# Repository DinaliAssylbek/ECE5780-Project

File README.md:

Team Members:
Hayden Walpole; Undergraduate; Computer Engineering 
Andy Tran; Undergraduate; Computer Engineering 
Dinali Assylbek; Undergraduate; Computer Engineering
Stein Witt; Undergraduate; Mechanical Engineering

-File Directory-
CAD_FILES: file for the Platic Housing of our Watch Monitor
Datasheetes: BOM and datasheets for the given componants
HealthMonitor: Main Code file to be used to Flash the board with initialization and reading the sensor
Nucleo_Board_Testing: Code used to Test Dev board and Flashing with our 6-pin SWD cable.
PCB: PCB Scematic files and Board Design
Photos: Pictures of the development and debugging process. Also contains helpful refrence photos
Analog Discovery Code Attempts: Code we tried to use to communicate over I2C using Waveform with an analog discovery.

Milestone 4 Powerpoint presentation: https://1drv.ms/p/c/c447666567076377/EbAtq3pLUSZKpYCg5cf9b-IBzeUnjeowH9_FPiCp1k7Zxw?e=1KSI1v

You need to install the following for the STM32 VSCode extension to work.

-STMCubeIDE
-STMCubeMX
-STMCLT
-STMMCU
ECE 5780 – ReadMe Documentation
Project Name: Wearable Health Monitor 
Purpose:
The purpose of this project is to design, assemble, and program a custom PCB for a compact wearable device that allows a person to continuously monitor their heart rate and blood oxygen levels (SpO₂). The device provides real-time feedback when readings fall outside safe thresholds by using an onboard vibrating motor and status LEDs. It is intended to be a low-power, discreet health monitoring solution suitable for everyday use.
Functionality:
The Wearable Health Monitor includes the following features:
•	Real-Time Heart Rate Monitoring: Uses the MAX30102 optical sensor to continuously measure the user’s heart rate.
•	SpO₂ (Blood Oxygen) Monitoring: Calculates and updates the user’s oxygen saturation level every few seconds.
•	Vibration Motor and Status LED: Activates when heart rate or oxygen levels are outside the defined safe range.
•	Power Supply: Currently powered via USB-C. However, the board can run on a battery if connected through the USB-C port (e.g., with a USB-C battery pack).

•	Optional Bluetooth: The board supports Bluetooth; however, Bluetooth functionality is not implemented in the driver code.

Setup Instructions:
1.	PCB Fabrication:
To manufacture the board, use the schematic and PCB layout files found in the PCB directory of the GitHub repository. These files are compatible with common PCB manufacturers such as PCBWay (used for this project). Before submission, make sure to generate and include:
o	Gerber files
o	Bill of Materials (BOM)
o	Pick-and-place files (if needed)
The schematic for this project is presented below: 
 
2.	Assembly Guidelines:
Component assembly is a critical step due to the small form factor and use of QFN or similar packages that do not expose all pins. Many components have pads located underneath, making traditional soldering difficult.
Important:
Avoid using a reflow oven. While convenient, reflow can result in unreliable connections or floating components. Instead:
o	Use solder paste with a precision heat gun
o	Inspect each connection carefully under magnification
However, if your manufacturer offers services for PCB assembly, it is advisable to have them assemble the board for you. This is to avoid any potential problems regarding the PCB itself.
Note: Be careful when handling the board after assembly, the parts are delicate!
3.	Programming the Board:
The board is programmed using a dedicated ST-Link programmer with a 6-pin Tag-Connect cable.
o	To enter bootloader mode:
	Power the board
	Press and hold the BOOT button
	Momentarily ground the NRST (reset) pin (accessible via the ST-Link header)
	Release NRST while continuing to hold BOOT for a few seconds
Note: While USB-C bootloader programming is theoretically possible, it has not been tested. The ST-Link method is the recommended and verified approach.
When using the ST-Link, bootloader mode is not required.
4.	Firmware Setup:
o	Clone the repository and open the Health Monitor project
o	All source files are in the Core directory
o	A custom library for the MAX30102 sensor is included
Pin Configuration:
o	PB8 → I2C1_SCL (Clock Line)
o	PB9 → I2C1_SDA (Data Line)
o	Pin 12 → Controls both the vibration motor and status LED
The project builds and runs best using the STM32CubeIDE and STM32CubeProgrammer.
Once the board is powered and connected via ST-Link:
o	Build the project
o	Flash the firmware using the programmer
o	The device will begin operation immediately after flashing

5.	Troubleshooting
In the case where you may encounter issues with the PCB, there are several steps you can take to diagnose and resolve problems:
o	No Power to the Board:
o	Confirm that the USB-C cable is securely connected and providing power. If not, try to use a different cable to supply power to the chip
o	Check the voltages along all the voltage lines (3.3V and 1.8V) using a multimeter.
o	Ensure all power-related components (LDO regulator, bypass caps, etc.) are properly soldered. If the board starts to heat up rapidly, use a thermal camera to help check for shorts.
o	Sensor Not Detected (MAX30102):
o	Double-check I2C connections (PB8 for SCL, PB9 for SDA).
o	Use a logic analyzer or oscilloscope to verify I2C traffic.
o	Confirm the sensor that the registers and addresses are configured correctly.
o	Programming Issues:
o	Make sure the ST-Link is correctly connected via the Tag-Connect header.
o	Ensure that the Tag-Connect and ST-Link work. This can be achieved by uploading code to a breakout board.
o	Ensure that all user code lies in the correct regions as defined in the cube IDE. Check that all the correct header files are included and desired code is not commented out.
o	Miscellaneous Issues:
o	If the PCB fails to work, inspect solder joints again for bridges or incomplete connections. Examine under a microscope. If possible, reach out to someone with a more trained eye to look at the soldering job.
o	Make sure components on the board are assembled correctly. This means making sure the orientations of the components are in the right place, and no components are missing.
o	Be careful when disconnecting the cable when flashing the board. This potentially could cause you to brick the chip on the PCB. 

Videos Used as Refrences:
Schematic Design Video: https://www.youtube.com/watch?v=nkHFoxe0mrU
PBC Design Video: https://www.youtube.com/watch?v=PlXd3lLZ4vc&t=10184s

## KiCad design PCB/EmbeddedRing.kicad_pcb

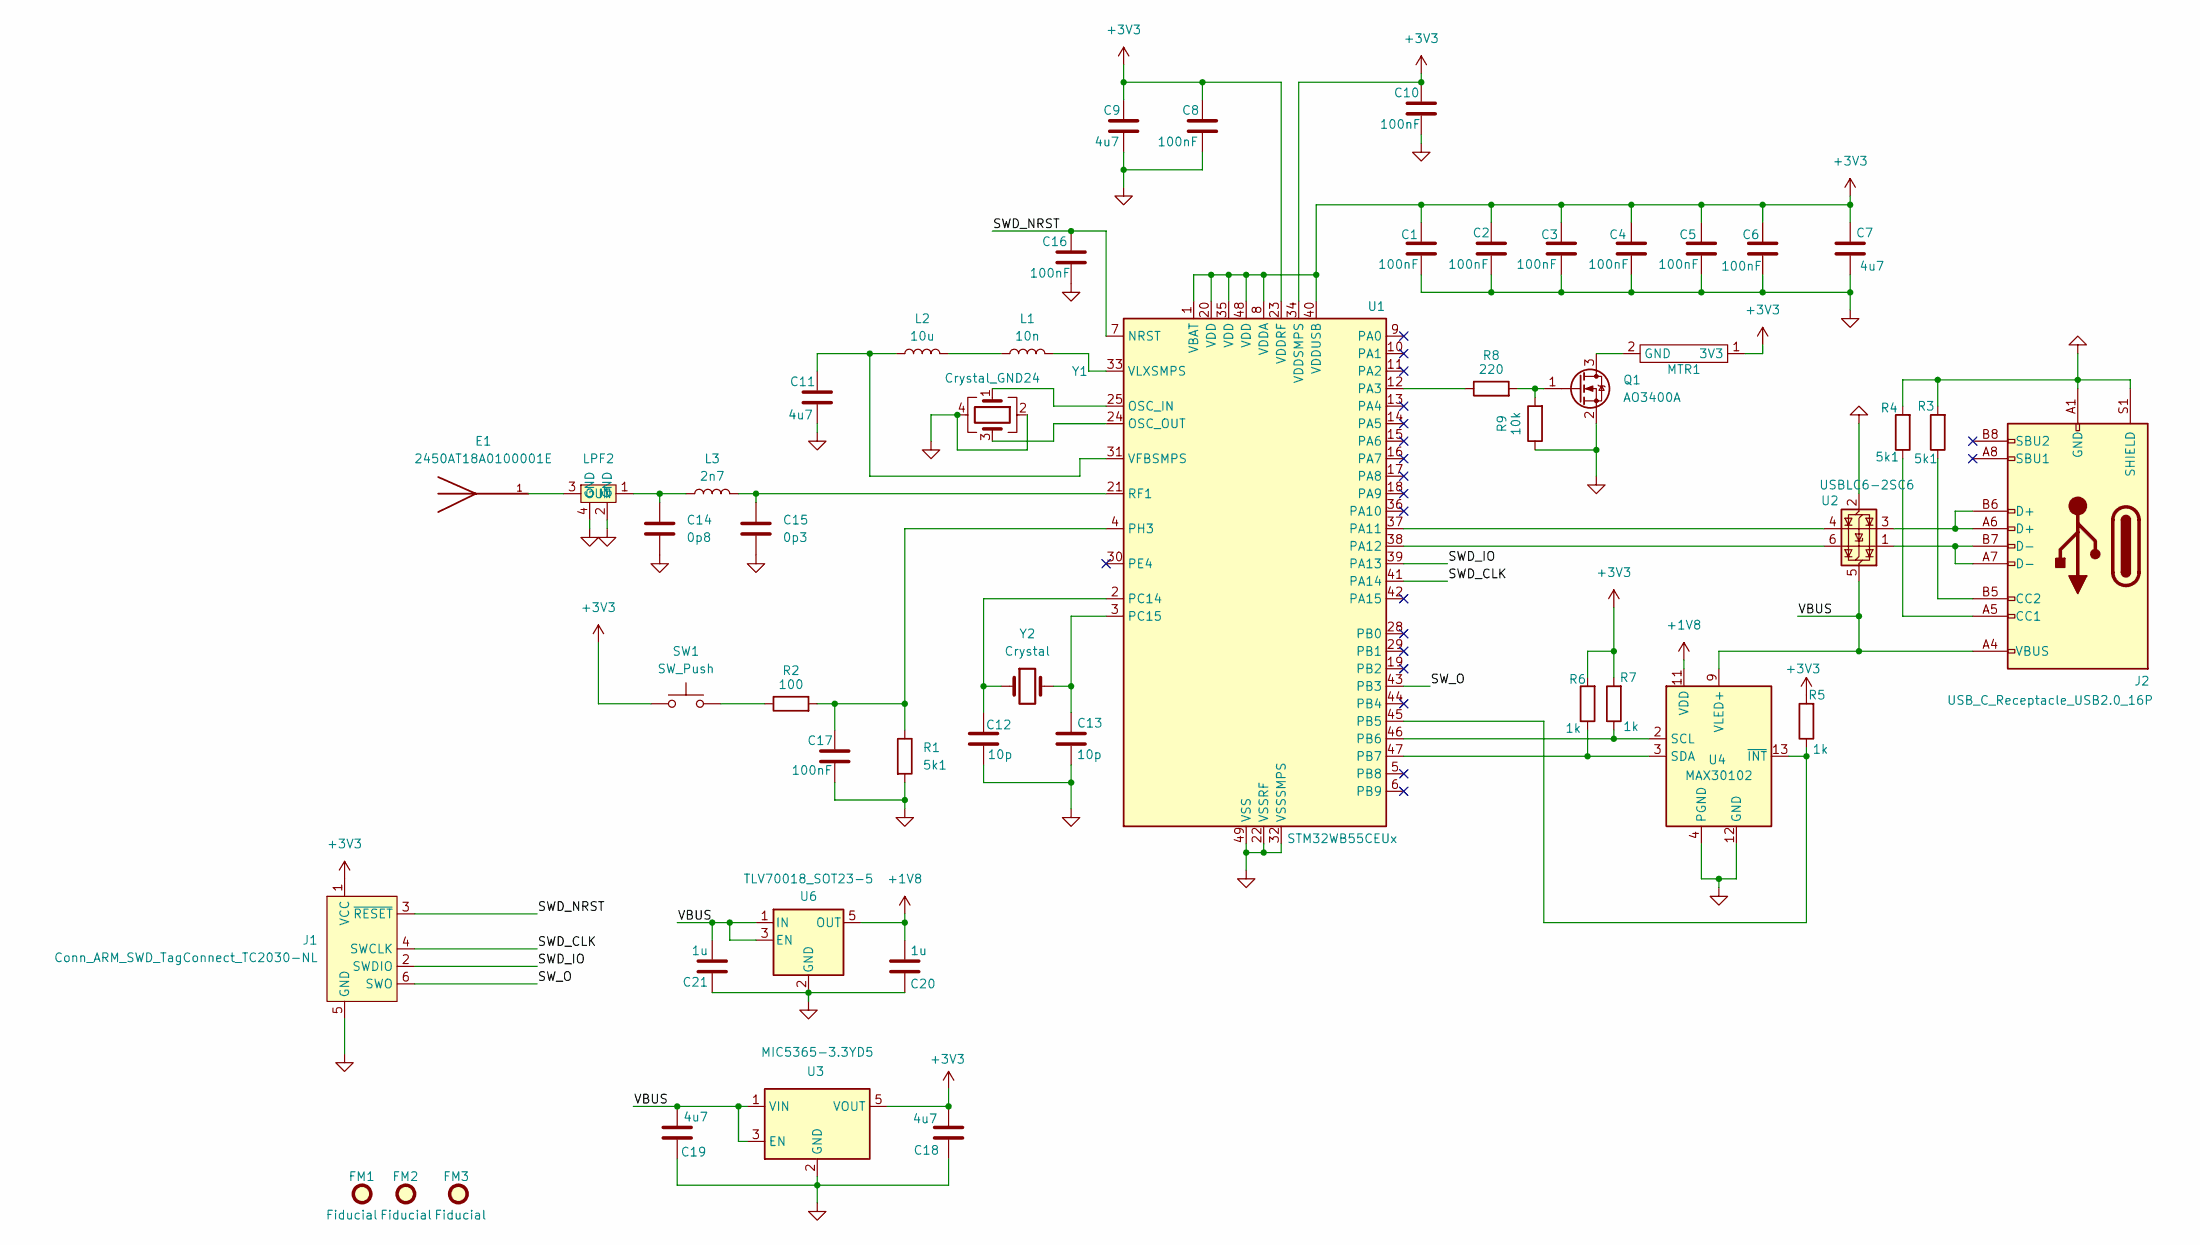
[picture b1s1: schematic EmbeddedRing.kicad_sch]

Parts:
C1, C2, C3, C4, C5, C6, C8, C10, C16, C17: 100nF; C_0402_1005Metric; Manufacturer Part Number 04026C104KAT2A
C7: 4u7; C_0603_1608Metric; Manufacturer Part Number 0603YD475MAT2A
C9, C11: 4u7; C_0402_1005Metric_Pad0.74x0.62mm_HandSolder; Manufacturer Part Number 0603YD475MAT2A
C12, C13: 10p; C_01005_0402Metric; Manufacturer Part Number KGM05ACG1H100JN
C14: 0p8; C_01005_0402Metric; Manufacturer Part Number GRM1555C1HR80BA01D
C15: 0p3; C_01005_0402Metric; Manufacturer Part Number GRM1555C1HR30WA01D
C18, C19: 4u7; C_0201_0603Metric_Pad0.64x0.40mm_HandSolder; Manufacturer Part Number 0603YD475MAT2A
C20, C21: 1u; C_0201_0603Metric_Pad0.64x0.40mm_HandSolder; Manufacturer Part Number 0603B105K100XD
E1: 2450AT18A0100001E; antennaa; PARTREV 4.0
FM1, FM2, FM3: Fiducial; Fiducial_0.5mm_Mask1.5mm
J1: Conn_ARM_SWD_TagConnect_TC2030-NL; Tag-Connect_TC2030-IDC-NL_2x03_P1.27mm_Vertical
J2: USB_C_Receptacle_USB2.0_16P; USB_C_Receptacle_GCT_USB4085; Manufacturer Part Number USB4085-GF-A
L1: 10n; L_0402_1005Metric; Manufacturer Part Number LQG15WZ10NJ02D
L2: 10u; L_0402_1005Metric; Manufacturer Part Number LQM21FN100M70L
L3: 2n7; L_01005_0402Metric; Manufacturer Part Number LQG15HS2N7S02D
LPF2: low-pass_filter-footprint; Manufacturer Part Number DLF162500LT-5028A1
MTR1: motor pad
Q1: AO3400A; SOT-23; Manufacturer Part Number AO3400A
R1, R3, R4: 5k1; R_0402_1005Metric; Manufacturer Part Number RC0603FR-075K1L
R2: 100; R_0402_1005Metric; Manufacturer Part Number RC0402JR-07100RL
R5, R6, R7: 1k; R_0402_1005Metric; Manufacturer Part Number RC0402JR-071KL
R8: 220; R_0402_1005Metric; Manufacturer Part Number RC0402JR-07100RL
R9: 10k; R_0402_1005Metric; Manufacturer Part Number RC0402JR-07100RL
SW1: SW_Push; SW_SPST_CK_RS282G05A3; Manufacturer Part Number RS-282G05A3-SM RT
U1: STM32WB55CEUx; stm32wb55; Manufacturer Part Number STM32WB55CEU6
U2: USBLC6-2SC6; SOT-23-6; Manufacturer Part Number USBLC6-2SC6
U3: MIC5365-3.3YD5; SOT-23-5; Manufacturer Part Number MIC5365-3.3YD5-TR
U4: MAX30102; heart_rate_sensor; Manufacturer Part Number MAX30102EFD+T
U6: TLV70018_SOT23-5; SOT-23-5; Manufacturer Part Number TLV77318PDBVR
Y1: Crystal_GND24; 32M_Crystal; Manufacturer Part Number CS06465-32M
Y2: Crystal; 32k_Crystal; Manufacturer Part Number STDMUB1-32.768K

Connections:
+1V8: C20.1, U4.11 (VDD), U6.5 (OUT)
+3V3: C1.1, C2.1, C3.1, C4.1, C5.1, C6.1, C7.1, C8.1, C9.1, C10.1, C18.1, J1.1 (VCC), MTR1.1 (3V3), R5.2, R6.2, R7.2, SW1.1, U1.1 (VBAT), U1.8 (VDDA), U1.20 (VDD), U1.23 (VDDRF), U1.34 (VDDSMPS), U1.35 (VDD), U1.40 (VDDUSB), U1.48 (VDD), U3.5 (VOUT)
/SWD_CLK: J1.4 (SWCLK), U1.41 (PA14)
/SWD_IO: J1.2 (SWDIO), U1.39 (PA13)
/SWD_NRST: C16.1, J1.3 (~RESET), U1.7 (NRST)
/SW_O: J1.6 (SWO), U1.43 (PB3)
/VBUS: C19.1, C21.1, J2.A4 (VBUS), J2.A9 (VBUS), J2.B4 (VBUS), J2.B9 (VBUS), U2.5 (VBUS), U3.1 (VIN), U3.3 (EN), U4.9 (VLED+), U4.10 (VLED+), U6.1 (IN), U6.3 (EN)
GND: C1.2, C2.2, C3.2, C4.2, C5.2, C6.2, C7.2, C8.2, C9.2, C10.2, C11.2, C12.2, C13.2, C14.2, C15.2, C16.2, C17.2, C18.2, C19.2, C20.2, C21.2, J1.5 (GND), J2.A1 (GND), J2.A12 (GND), J2.B1 (GND), J2.B12 (GND), J2.S1 (SHIELD), LPF2.2 (GND), LPF2.4 (GND), Q1.2 (S), R1.2, R3.2, R4.2, R9.1, U1.22 (VSSRF), U1.32 (VSSSMPS), U1.49 (VSS), U2.2 (GND), U3.2 (GND), U4.4 (PGND), U4.12 (GND), U6.2 (GND), Y1.2, Y1.4
unnamed: J2.A5 (CC1), R4.1
unnamed: J2.B5 (CC2), R3.1
unnamed: J2.A6 (D+), J2.B6 (D+), U2.3 (I/O2)
unnamed: J2.A7 (D-), J2.B7 (D-), U2.1 (I/O1)
unnamed: L1.1, L2.2
unnamed: C14.1, L3.1, LPF2.1 (IN)
unnamed: E1.1, LPF2.3 (OUT)
unnamed: MTR1.2 (GND), Q1.3 (D)
unnamed: Q1.1 (G), R8.2, R9.2
unnamed: R2.1, SW1.2
unnamed: U1.25 (OSC_IN), Y1.1
unnamed: U1.24 (OSC_OUT), Y1.3
unnamed: R8.1, U1.12 (PA3)
unnamed: U1.37 (PA11), U2.4 (I/O2)
unnamed: U1.38 (PA12), U2.6 (I/O1)
unnamed: R5.1, U1.45 (PB5), U4.13 (~INT)
unnamed: R7.1, U1.46 (PB6), U4.2 (SCL)
unnamed: R6.1, U1.47 (PB7), U4.3 (SDA)
unnamed: C12.1, U1.2 (PC14), Y2.1
unnamed: C13.1, U1.3 (PC15), Y2.2
unnamed: C17.1, R1.1, R2.2, U1.4 (PH3)
unnamed: C15.1, L3.2, U1.21 (RF1)
unnamed: C11.1, L2.1, U1.31 (VFBSMPS)
unnamed: L1.2, U1.33 (VLXSMPS)

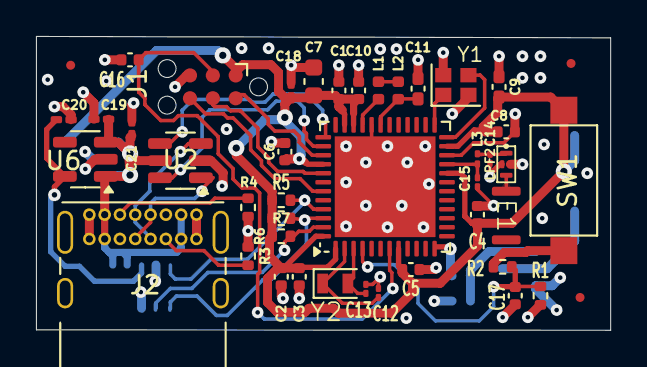
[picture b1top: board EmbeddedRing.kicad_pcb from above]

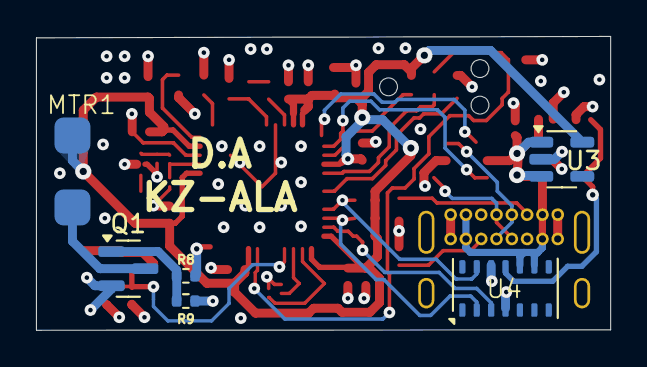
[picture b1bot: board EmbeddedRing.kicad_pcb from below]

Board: 4 copper layers, 31.9 x 16.3 mm, 50 parts (6 on the bottom side), 32 nets.

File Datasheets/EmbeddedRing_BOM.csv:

"Reference","Value","Datasheet","Footprint","Qty","DNP","Distributer Link","Manufacturer","Manufacturer Part Number"
"LPF2,MTR1","~","","-- mixed values --","2","","-- mixed values --","-- mixed values --","-- mixed values --"
"C20,C21","1u","~","Capacitor_SMD:C_0201_0603Metric_Pad0.64x0.40mm_HandSolder","2","","https://www.digikey.com/en/products/detail/nextgen-component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","Aillen","0603B105K100XD"
"Q1","AO3400A","http://www.aosmd.com/pdfs/datasheet/AO3400A.pdf","Package_TO_SOT_SMD:SOT-23","1","","https://www.digikey.com/en/products/detail/alpha-omega-semic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","Alpha & Omega Semiconductor Inc.","AO3400A"
"U4","MAX30102","https://datasheets.maximintegrated.com/en/ds/MAX30102.pdf","low_pass_filter:heart_rate_sensor","1","","https://www.digikey.com/en/products/detail/analog-devices-in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","Analog Devices Inc./Maxim Integrated","MAX30102EFD+T"
"SW1","SW_Push","~","Button_Switch_SMD:SW_SPST_CK_RS282G05A3","1","","https://www.digikey.com/en/products/detail/c-k/RS-282G05A3-S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","C&K","RS-282G05A3-SM RT"
"J2","USB_C_Receptacle_USB2.0_16P","https://www.usb.org/sites/default/files/documents/usb_type-c.zip","Connector_USB:USB_C_Receptacle_GCT_USB4085","1","","https://www.digikey.com/en/products/detail/gct/USB4085-GF-A/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","GCT","USB4085-GF-A"
"E1","2450AT18A0100001E","","low_pass_filter:antennaa","1","","https://www.digikey.com/en/products/detail/johanson-technolo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","Johanson Technology Inc.","2450AT18A0100001E"
"C1,C2,C3,C4,C5,C6,C8,C10,C16,C17","100nF","~","Capacitor_SMD:C_0402_1005Metric","10","","https://www.digikey.com/en/products/detail/kyocera-avx/04026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","KYOCERA AVX","04026C104KAT2A"
"C7,C9,C11,C18,C19","4u7","~","-- mixed values --","5","","https://www.digikey.com/en/products/detail/kyocera-avx/0603Y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","KYOCERA AVX","0603YD475MAT2A"
"C12,C13","10p","~","Capacitor_SMD:C_01005_0402Metric","2","","https://www.digikey.com/en/products/detail/kyocera-avx/KGM05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","KYOCERA AVX","KGM05ACG1H100JN"
"U3","MIC5365-3.3YD5","http://ww1.microchip.com/downloads/en/DeviceDoc/mic5365.pdf","Package_TO_SOT_SMD:SOT-23-5","1","","https://www.digikey.com/en/products/detail/microchip-technol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","Microchip Technology","MIC5365-3.3YD5-TR"
"C14","0p8","~","Capacitor_SMD:C_01005_0402Metric","1","","https://www.digikey.com/en/products/detail/murata-electronic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","Murata Electronics","GRM1555C1HR80BA01D"
"C15","0p3","~","Capacitor_SMD:C_01005_0402Metric","1","","https://www.digikey.com/en/products/detail/murata-electronic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","Murata Electronics","GRM1555C1HR30WA01D"
"L1","10n","~","Inductor_SMD:L_0402_1005Metric","1","","https://www.digikey.com/en/products/detail/murata-electronic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","Murata Electronics","LQG15WZ10NJ02D"
"L2","10u","~","Inductor_SMD:L_0402_1005Metric","1","","https://www.digikey.com/en/products/detail/murata-electronic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","Murata Electronics","LQM21FN100M70L"
"L3","2n7","~","Inductor_SMD:L_01005_0402Metric","1","","https://www.digikey.com/en/products/detail/murata-electronic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","Murata Electronics","LQG15HS2N7S02D"
"Y1","Crystal_GND24","~","low_pass_filter:32M_Crystal","1","","https://www.digikey.com/en/products/detail/ndk-nihon-dempa-k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","NDK (NIHON DEMPA KOGYO CO., LTD)","CS06465-32M"
"Y2","Crystal","~","low_pass_filter:32k_Crystal","1","","https://www.digikey.com/en/products/detail/ndk-nihon-dempa-k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","NDK (NIHON DEMPA KOGYO CO., LTD)","STDMUB1-32.768K"
"U1","STM32WB55CEUx","https://www.st.com/resource/en/datasheet/stm32wb55ce.pdf","low_pass_filter:stm32wb55","1","","https://www.digikey.com/en/products/detail/stmicroelectronic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","STMicroelectronics","STM32WB55CEU6"
"U2","USBLC6-2SC6","https://www.st.com/resource/en/datasheet/usblc6-2.pdf","Package_TO_SOT_SMD:SOT-23-6","1","","https://www.digikey.com/en/products/detail/stmicroelectronic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","STMicroelectronics","USBLC6-2SC6"
"U6","TLV70018_SOT23-5","http://www.ti.com/lit/ds/symlink/tlv700.pdf","Package_TO_SOT_SMD:SOT-23-5","1","","https://www.digikey.com/en/products/detail/texas-instruments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","Texas Instruments","TLV77318PDBVR"
"R1,R3,R4","5k1","~","Resistor_SMD:R_0402_1005Metric","3","","https://www.digikey.com/en/products/detail/yageo/RC0603FR-07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","YAGEO","RC0603FR-075K1L"
"R2","100","~","Resistor_SMD:R_0402_1005Metric","1","","https://www.digikey.com/en/products/detail/yageo/RC0402JR-07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","YAGEO","RC0402JR-07100RL"
"R5,R6,R7","1k","~","Resistor_SMD:R_0402_1005Metric","3","","https://www.digikey.com/en/products/detail/yageo/RC0402JR-07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","YAGEO","RC0402JR-071KL"
"R8","220","~","Resistor_SMD:R_0402_1005Metric","1","","https://www.digikey.com/en/products/detail/yageo/RC0402JR-07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","YAGEO","RC0402JR-07100RL"
"R9","10k","~","Resistor_SMD:R_0402_1005Metric","1","","https://www.digikey.com/en/products/detail/yageo/RC0402JR-07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","YAGEO","RC0402JR-07100RL"

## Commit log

2025-03-21 test
    added group members to readme file to check push access
2025-03-25 Testing commit permissions for Milestone 0
2025-03-25 Hayden Milestone 0
2025-03-26 Dinali's Commit
2025-03-28 Stein Witt's (u1090350) commit
2025-03-28 Stein Witt (u1090350) changed README for Milestone 0
2025-04-02 Got LED blinking using STM32 CubeIDE
2025-04-11 Added CAD models folder and started designing enclosure in SolidWorks
2025-04-21 Added A folder for Photos and added the pictures from the microscope
2025-04-21 Update README.md with Documentation Link
2025-04-22 psuedo code for reading data from hr sensor
2025-04-22 Added more pictures fromt he design process
2025-04-23 Added Max30102 header file
2025-04-23 Added Max30102 c file
2025-04-23 Added start of Documentation Draft
2025-04-24 Working Code
2025-04-24 Updated Readme and Added the DataSheets for the DevBoard
2025-04-24 Tried using analog discovery to talk to the Sensor, added code attempt to repo
2025-04-25 updated ppt
2025-04-25 Combined word README doc into main file
